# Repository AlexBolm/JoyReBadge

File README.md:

# JoyreBadge
Software for JoyReBadge (STM32F103C8T6 chip) made in CooCox 2.0.7

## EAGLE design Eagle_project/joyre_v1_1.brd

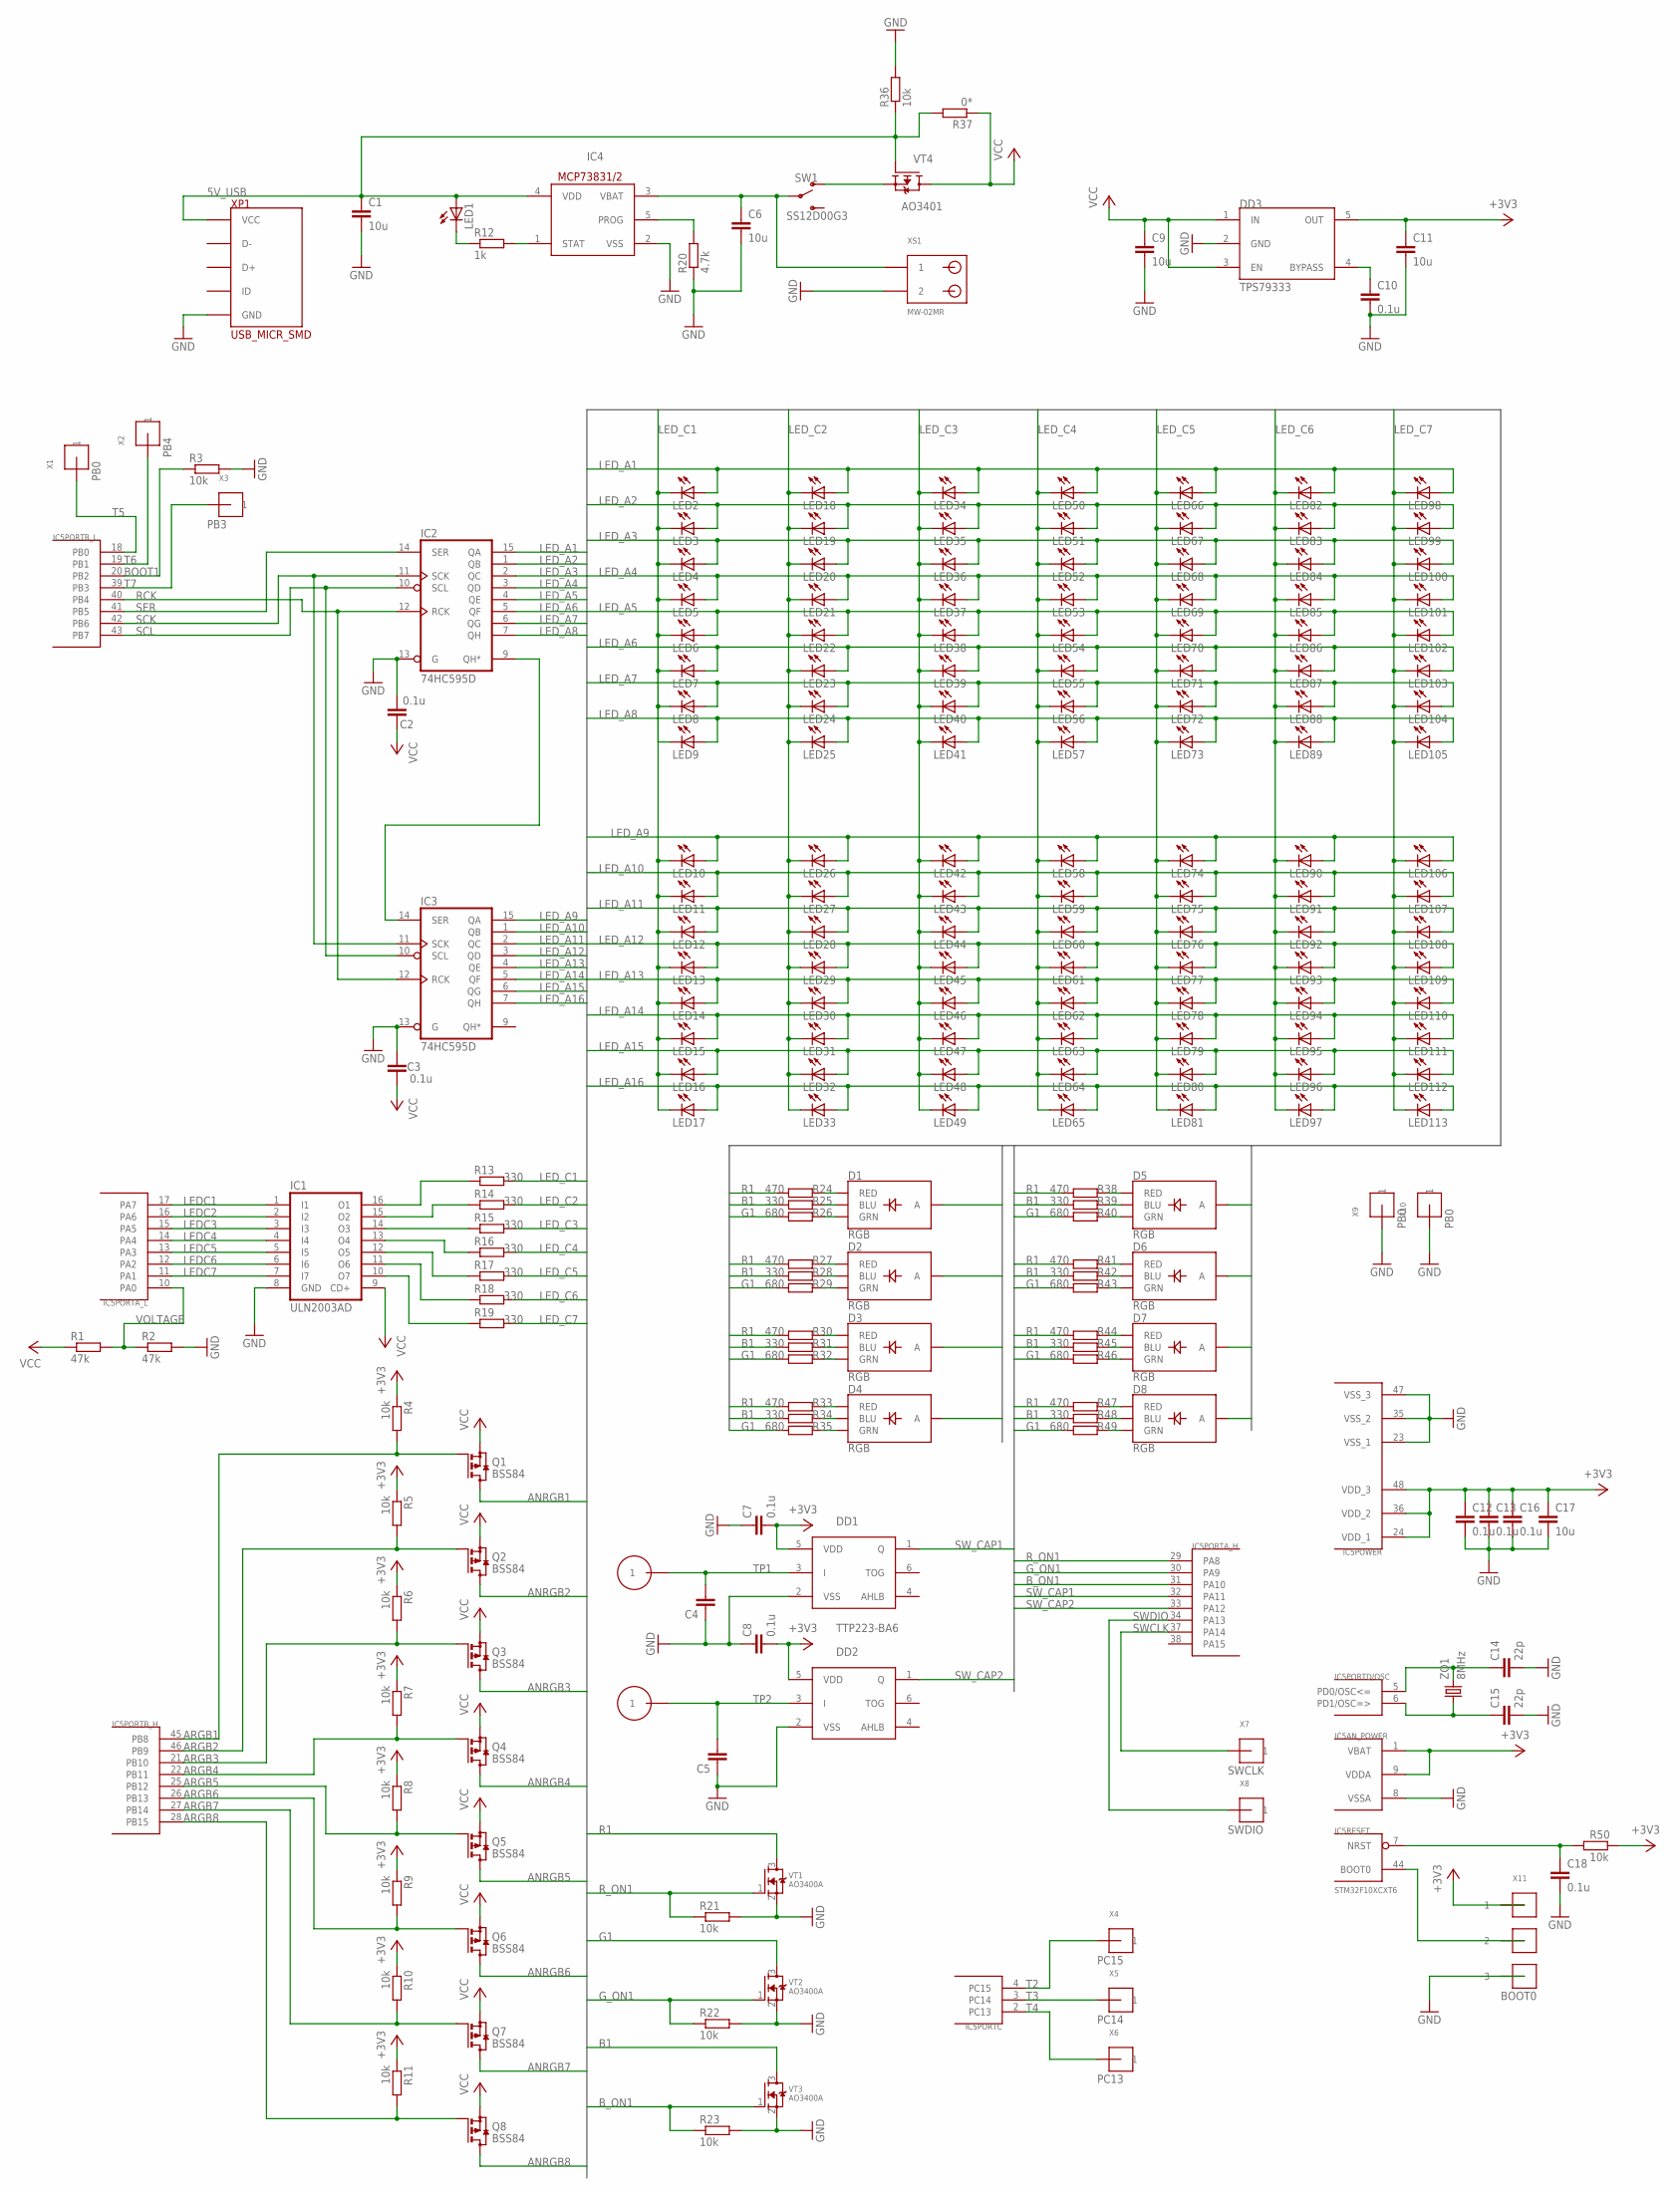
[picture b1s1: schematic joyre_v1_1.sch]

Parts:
C1, C6, C9, C11, C17: 10u; C1206K
C2, C3, C7, C8, C10, C12, C13, C16, C18: 0.1u; C0603K
C4, C5: C-EUC0603K; C0603K
C14, C15: 22p; C0603K
D1, D2, D3, D4, D5, D6, D7, D8: RGB; P-LCC-4-3
DD1, DD2: TTP223-BA6; TSOT23-6
DD3: TPS79333; DBV_R-PDSO-G5
IC1: ULN2003AD; SO16
IC2, IC3: 74HC595D; SO16
IC4: MCP73831/OT; SOT23-5L
IC5: STM32F10XCXT6; TQFP48
LED1, LED2, LED3, LED4, LED5, LED6, LED7, LED8, LED9, LED10, LED11, LED12, LED13, LED14, LED15, LED16, LED17, LED18, LED19, LED20, LED21, LED22, LED23, LED24, LED25, LED26, LED27, LED28, LED29, LED30, LED31, LED32, LED33, LED34, LED35, LED36, LED37, LED38, LED39, LED40, LED41, LED42, LED43, LED44, LED45, LED46, LED47, LED48, LED49, LED50, LED51, LED52, LED53, LED54, LED55, LED56, LED57, LED58, LED59, LED60, LED61, LED62, LED63, LED64, LED65, LED66, LED67, LED68, LED69, LED70, LED71, LED72, LED73, LED74, LED75, LED76, LED77, LED78, LED79, LED80, LED81, LED82, LED83, LED84, LED85, LED86, LED87, LED88, LED89, LED90, LED91, LED92, LED93, LED94, LED95, LED96, LED97, LED98, LED99, LED100, LED101, LED102, LED103, LED104, LED105, LED106, LED107, LED108, LED109, LED110, LED111, LED112, LED113: LEDCHIPLED_0805; CHIPLED_0805
Q1, Q2, Q3, Q4, Q5, Q6, Q7, Q8: BSS84; SOT23
R1, R2: 47k; R0603
R3, R4, R5, R6, R7, R8, R9, R10, R11, R21, R22, R23, R36, R50: 10k; R0603
R12: 1k; R0603
R13, R14, R15, R16, R17, R18, R19, R25, R28, R31, R34, R39, R42, R45, R48: 330; R0603
R20: 4.7k; R0603
R24, R27, R30, R33, R38, R41, R44, R47: 470; R0603
R26, R29, R32, R35, R40, R43, R46, R49: 680; R0603
R37: 0*; R0603
SW1: SS12D00G3
VT1, VT2, VT3: AO3400A; SOT23
VT4: AO3401; SOT23
X1, X9, X10: PB0; 1PIN_SMD_3X2
X2: PB4; 1PIN_SMD_3X2
X3: PB3; 1PIN_SMD_3X2
X4: PC15; 1PIN_SMD_3X2
X5: PC14; 1PIN_SMD_3X2
X6: PC13; 1PIN_SMD_3X2
X7: SWCLK; 1PIN_SMD_3X2
X8: SWDIO; 1PIN_SMD_3X2
X11: BOOT0; 3PIN_SOLDER
XC1, XC2: CAP_PIN
XP1: USB_MICR_SMD
XS1: MW-02MR; CWF-2R
ZQ1: 8MHz; HC49SM

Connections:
5V_USB: C1.1, IC4.4 (VDD), LED1.A, R36.1, R37.2, VT4.1 (G), XP1.P$1 (VCC)
+3V3: C7.2, C8.2, C11.1, C12.1, C13.1, C16.1, C17.1, DD1.5 (VDD), DD2.5 (VDD), DD3.5 (OUT), IC5.1 (VBAT), IC5.9 (VDDA), IC5.24 (VDD_1), IC5.36 (VDD_2), IC5.48 (VDD_3), R4.1, R5.1, R6.1, R7.1, R8.1, R9.1, R10.1, R11.1, R50.2, X11.1
ANRGB1: D1.4 (A), Q1.3 (D)
ANRGB2: D2.4 (A), Q2.3 (D)
ANRGB3: D3.4 (A), Q3.3 (D)
ANRGB4: D4.4 (A), Q4.3 (D)
ANRGB5: D5.4 (A), Q5.3 (D)
ANRGB6: D6.4 (A), Q6.3 (D)
ANRGB7: D7.4 (A), Q7.3 (D)
ANRGB8: D8.4 (A), Q8.3 (D)
ARGB1: IC5.45 (PB8), Q1.1 (G), R4.2
ARGB2: IC5.46 (PB9), Q2.1 (G), R5.2
ARGB3: IC5.21 (PB10), Q3.1 (G), R6.2
ARGB4: IC5.22 (PB11), Q4.1 (G), R7.2
ARGB5: IC5.25 (PB12), Q5.1 (G), R8.2
ARGB6: IC5.26 (PB13), Q6.1 (G), R9.2
ARGB7: IC5.27 (PB14), Q7.1 (G), R10.2
ARGB8: IC5.28 (PB15), Q8.1 (G), R11.2
B1: R25.1, R28.1, R31.1, R34.1, R39.1, R42.1, R45.1, R48.1, VT3.3 (D)
BOOT1: IC5.20 (PB2), R3.1
B_ON1: IC5.31 (PA10), R23.1, VT3.1 (G)
G1: R26.1, R29.1, R32.1, R35.1, R40.1, R43.1, R46.1, R49.1, VT2.3 (D)
GND: C1.2, C2.2, C3.2, C4.1, C5.1, C6.2, C7.1, C8.1, C9.2, C10.2, C11.2, C12.2, C13.2, C14.2, C15.2, C16.2, C17.2, C18.2, DD1.2 (VSS), DD2.2 (VSS), DD3.2 (GND), IC1.8 (GND), IC2.8 (GND), IC2.13 (G), IC3.8 (GND), IC3.13 (G), IC4.2 (VSS), IC5.8 (VSSA), IC5.23 (VSS_1), IC5.35 (VSS_2), IC5.47 (VSS_3), R2.2, R3.2, R20.1, R21.2, R22.2, R23.2, R36.2, VT1.2 (S), VT2.2 (S), VT3.2 (S), X9.P$1, X10.P$1, X11.3, XP1.P$5 (GND), XS1.P$2 (2)
G_ON1: IC5.30 (PA9), R22.1, VT2.1 (G)
LEDC1: IC1.1 (I1), IC5.17 (PA7)
LEDC2: IC1.2 (I2), IC5.16 (PA6)
LEDC3: IC1.3 (I3), IC5.15 (PA5)
LEDC4: IC1.4 (I4), IC5.14 (PA4)
LEDC5: IC1.5 (I5), IC5.13 (PA3)
LEDC6: IC1.6 (I6), IC5.12 (PA2)
LEDC7: IC1.7 (I7), IC5.11 (PA1)
LED_A1: IC2.15 (QA), LED2.A, LED18.A, LED34.A, LED50.A, LED66.A, LED82.A, LED98.A
LED_A2: IC2.1 (QB), LED3.A, LED19.A, LED35.A, LED51.A, LED67.A, LED83.A, LED99.A
LED_A3: IC2.2 (QC), LED4.A, LED20.A, LED36.A, LED52.A, LED68.A, LED84.A, LED100.A
LED_A4: IC2.3 (QD), LED5.A, LED21.A, LED37.A, LED53.A, LED69.A, LED85.A, LED101.A
LED_A5: IC2.4 (QE), LED6.A, LED22.A, LED38.A, LED54.A, LED70.A, LED86.A, LED102.A
LED_A6: IC2.5 (QF), LED7.A, LED23.A, LED39.A, LED55.A, LED71.A, LED87.A, LED103.A
LED_A7: IC2.6 (QG), LED8.A, LED24.A, LED40.A, LED56.A, LED72.A, LED88.A, LED104.A
LED_A8: IC2.7 (QH), LED9.A, LED25.A, LED41.A, LED57.A, LED73.A, LED89.A, LED105.A
LED_A9: IC3.15 (QA), LED10.A, LED26.A, LED42.A, LED58.A, LED74.A, LED90.A, LED106.A
LED_A10: IC3.1 (QB), LED11.A, LED27.A, LED43.A, LED59.A, LED75.A, LED91.A, LED107.A
LED_A11: IC3.2 (QC), LED12.A, LED28.A, LED44.A, LED60.A, LED76.A, LED92.A, LED108.A
LED_A12: IC3.3 (QD), LED13.A, LED29.A, LED45.A, LED61.A, LED77.A, LED93.A, LED109.A
LED_A13: IC3.4 (QE), LED14.A, LED30.A, LED46.A, LED62.A, LED78.A, LED94.A, LED110.A
LED_A14: IC3.5 (QF), LED15.A, LED31.A, LED47.A, LED63.A, LED79.A, LED95.A, LED111.A
LED_A15: IC3.6 (QG), LED16.A, LED32.A, LED48.A, LED64.A, LED80.A, LED96.A, LED112.A
LED_A16: IC3.7 (QH), LED17.A, LED33.A, LED49.A, LED65.A, LED81.A, LED97.A, LED113.A
LED_C1: LED2.C, LED3.C, LED4.C, LED5.C, LED6.C, LED7.C, LED8.C, LED9.C, LED10.C, LED11.C, LED12.C, LED13.C, LED14.C, LED15.C, LED16.C, LED17.C, R13.2
LED_C2: LED18.C, LED19.C, LED20.C, LED21.C, LED22.C, LED23.C, LED24.C, LED25.C, LED26.C, LED27.C, LED28.C, LED29.C, LED30.C, LED31.C, LED32.C, LED33.C, R14.2
LED_C3: LED34.C, LED35.C, LED36.C, LED37.C, LED38.C, LED39.C, LED40.C, LED41.C, LED42.C, LED43.C, LED44.C, LED45.C, LED46.C, LED47.C, LED48.C, LED49.C, R15.2
LED_C4: LED50.C, LED51.C, LED52.C, LED53.C, LED54.C, LED55.C, LED56.C, LED57.C, LED58.C, LED59.C, LED60.C, LED61.C, LED62.C, LED63.C, LED64.C, LED65.C, R16.2
LED_C5: LED66.C, LED67.C, LED68.C, LED69.C, LED70.C, LED71.C, LED72.C, LED73.C, LED74.C, LED75.C, LED76.C, LED77.C, LED78.C, LED79.C, LED80.C, LED81.C, R17.2
LED_C6: LED82.C, LED83.C, LED84.C, LED85.C, LED86.C, LED87.C, LED88.C, LED89.C, LED90.C, LED91.C, LED92.C, LED93.C, LED94.C, LED95.C, LED96.C, LED97.C, R18.2
LED_C7: LED98.C, LED99.C, LED100.C, LED101.C, LED102.C, LED103.C, LED104.C, LED105.C, LED106.C, LED107.C, LED108.C, LED109.C, LED110.C, LED111.C, LED112.C, LED113.C, R19.2
unnamed: D1.1 (RED), R24.2
unnamed: D1.3 (BLU), R25.2
unnamed: D1.2 (GRN), R26.2
unnamed: D2.1 (RED), R27.2
unnamed: D2.3 (BLU), R28.2
unnamed: D2.2 (GRN), R29.2
unnamed: D3.2 (GRN), R32.2
unnamed: D3.3 (BLU), R31.2
unnamed: D3.1 (RED), R30.2
unnamed: D4.2 (GRN), R35.2
unnamed: D4.3 (BLU), R34.2
unnamed: D4.1 (RED), R33.2
unnamed: D8.2 (GRN), R49.2
unnamed: D8.3 (BLU), R48.2
unnamed: D8.1 (RED), R47.2
unnamed: D7.2 (GRN), R46.2
unnamed: D7.3 (BLU), R45.2
unnamed: D7.1 (RED), R44.2
unnamed: D6.2 (GRN), R43.2
unnamed: D6.3 (BLU), R42.2
unnamed: D6.1 (RED), R41.2
unnamed: D5.1 (RED), R38.2
unnamed: D5.3 (BLU), R39.2
unnamed: D5.2 (GRN), R40.2
unnamed: IC1.10 (O7), R19.1
unnamed: IC1.11 (O6), R18.1
unnamed: IC1.12 (O5), R17.1
unnamed: IC1.13 (O4), R16.1
unnamed: IC1.14 (O3), R15.1
unnamed: IC1.15 (O2), R14.1
unnamed: IC1.16 (O1), R13.1
unnamed: SW1.1 (O), VT4.2 (S)
unnamed: IC5.44 (BOOT0), X11.2
unnamed: IC2.9 (QH*), IC3.14 (SER)
unnamed: IC4.1 (STAT), R12.2
unnamed: C10.1, DD3.4 (BYPASS)
unnamed: IC4.5 (PROG), R20.2
unnamed: C6.1, IC4.3 (VBAT), SW1.2, XS1.P$1 (1)
unnamed: LED1.C, R12.1
unnamed: C14.1, IC5.5 (PD0/OSC<=), ZQ1.2
unnamed: C15.1, IC5.6 (PD1/OSC=>), ZQ1.1
unnamed: C18.1, IC5.7 (NRST), R50.1
R1: R24.1, R27.1, R30.1, R33.1, R38.1, R41.1, R44.1, R47.1, VT1.3 (D)
RCK: IC2.12 (RCK), IC3.12 (RCK), IC5.40 (PB4)
R_ON1: IC5.29 (PA8), R21.1, VT1.1 (G)
SCK: IC2.11 (SCK), IC3.11 (SCK), IC5.42 (PB6)
SCL: IC2.10 (SCL), IC3.10 (SCL), IC5.43 (PB7)
SER: IC2.14 (SER), IC5.41 (PB5)
SWCLK: IC5.37 (PA14), X7.P$1
SWDIO: IC5.34 (PA13), X8.P$1
SW_CAP1: DD1.1 (Q), IC5.32 (PA11)
SW_CAP2: DD2.1 (Q), IC5.33 (PA12)
T2: IC5.4 (PC15), X4.P$1
T3: IC5.3 (PC14), X5.P$1
T4: IC5.2 (PC13), X6.P$1
T5: IC5.18 (PB0), X1.P$1
T6: IC5.19 (PB1), X2.P$1
T7: IC5.39 (PB3), X3.P$1
TP1: C4.2, DD1.3 (I), XC1.P$1
TP2: C5.2, DD2.3 (I), XC2.P$1
VCC: C2.1, C3.1, C9.1, DD3.1 (IN), DD3.3 (EN), IC1.9 (CD+), IC2.16 (VCC), IC3.16 (VCC), Q1.2 (S), Q2.2 (S), Q3.2 (S), Q4.2 (S), Q5.2 (S), Q6.2 (S), Q7.2 (S), Q8.2 (S), R1.1, R37.1, VT4.3 (D)
VOLTAGE: IC5.10 (PA0), R1.2, R2.1

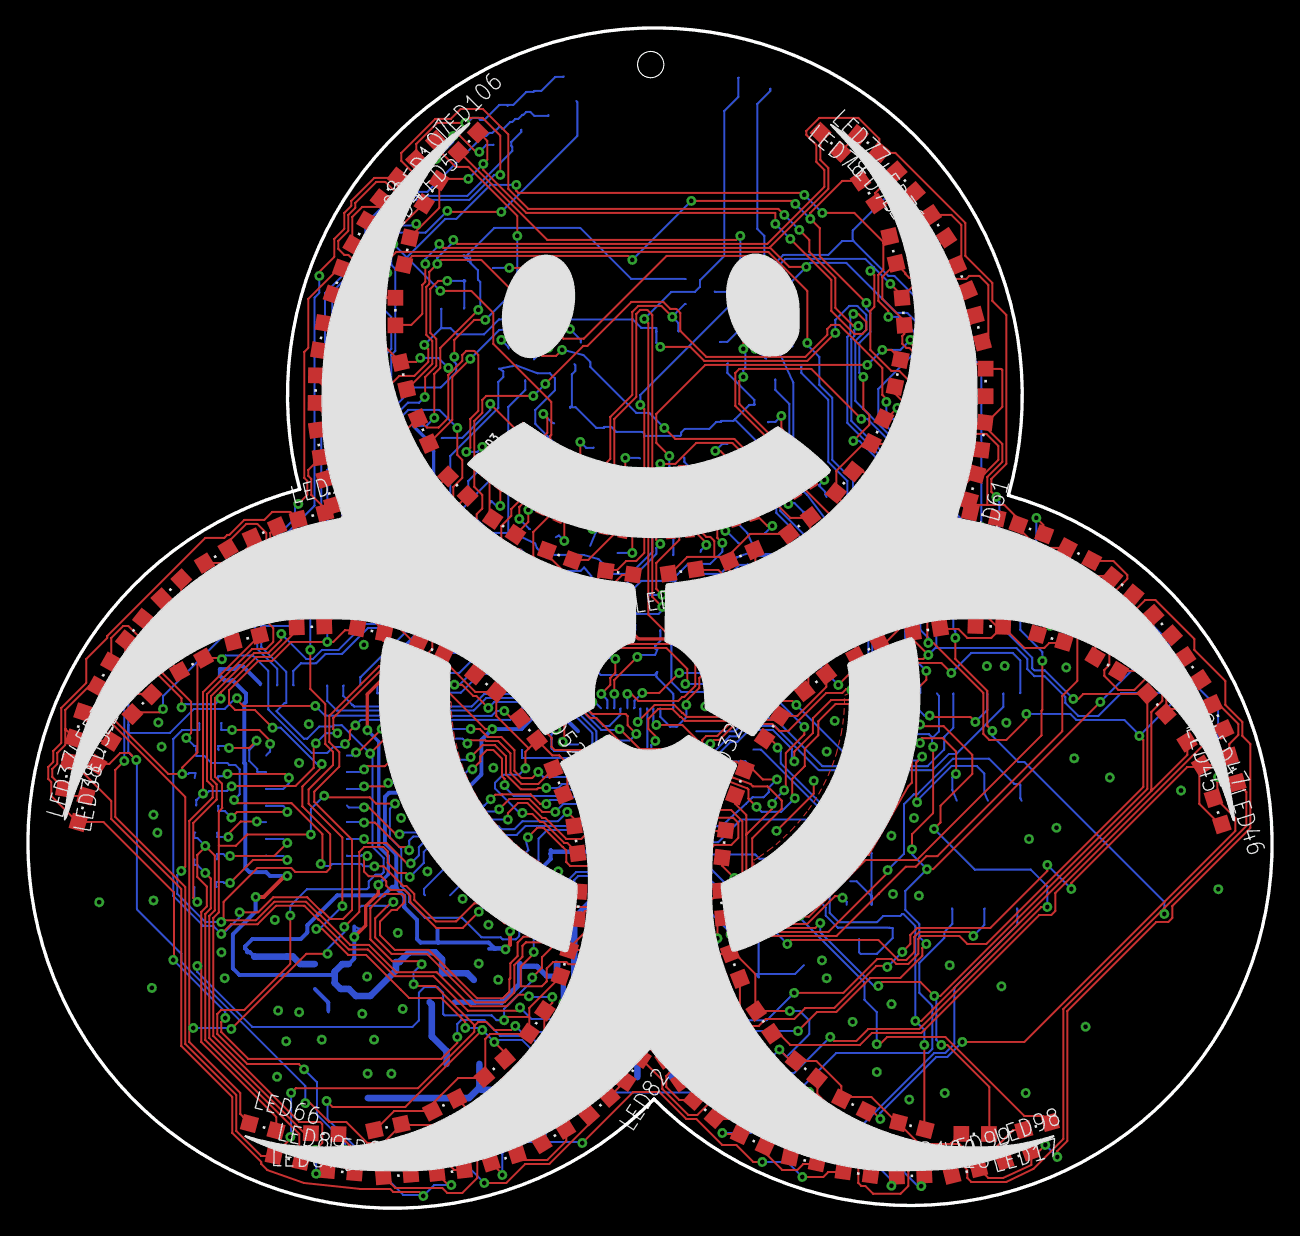
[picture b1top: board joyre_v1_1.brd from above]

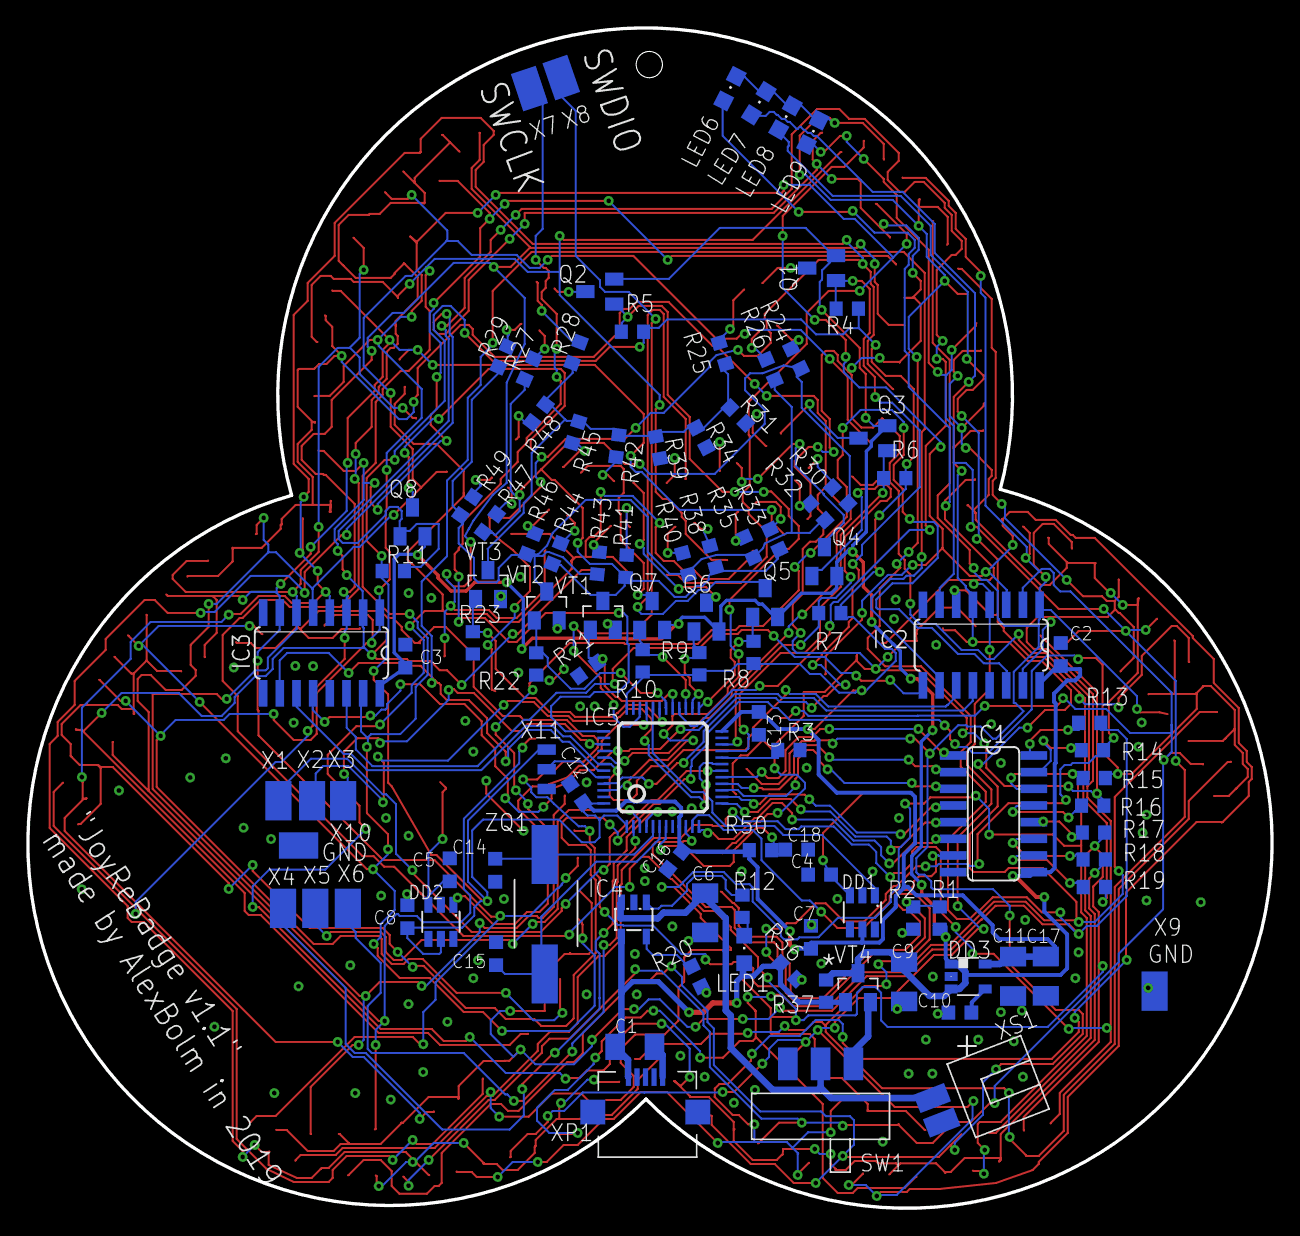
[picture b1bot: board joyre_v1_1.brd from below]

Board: 2 copper layers, 94.8 x 89.9 mm, 226 parts (108 on the bottom side), 116 nets.

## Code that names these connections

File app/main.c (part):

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#include "stm32f10x_rcc.h"
/*
 * ########  PIO  ###########
 * PA0 - lipo voltage ADC
 * PA1-PA7 - catodes of LED MATRIX
 * PA8 - RGB [R] catode
 * PA9 - RGB [G] catode
 * PA10 - RGB [B] catode
 * PA11 - capative touch button left
 * PA12 - capative touch button right
 * PA13 - SWDIO
 * PA14 - SWCLK
 *
 * PB0 - test pin
 * PB1 - test pin
 * PB2 - BOOT1
 * PB3 - test pin
 * PB4 - RCK (74HC595)
 * PB5 - SER (74HC595)
 * PB6 - SCK (74HC595)
 * PB7 - SCL (74HC595)
 * PB8-PB15 - RGB anodes
 *
 * PC13 - test
 * PC14 - test
 * PC15 - test
 */

#define DEBUG_ON GPIO_SetBits(GPIOB,GPIO_Pin_0)
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
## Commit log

2019-03-09 version 1.0
    11 modes + show voltage of Li-Po
2019-03-11 add sch and pcb
    Eagle 9.3.1
2019-03-11 some libs for eagle
    some libs for eagle

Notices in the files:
app/main.c:
Copyright (c) 2014 CooCox.  All rights reserved.
parts and their libraries:
SparkFun-LED: Licensing: Creative Commons ShareAlike 4.0 International - https://creativecommons.org/licenses/by-sa/4.0
